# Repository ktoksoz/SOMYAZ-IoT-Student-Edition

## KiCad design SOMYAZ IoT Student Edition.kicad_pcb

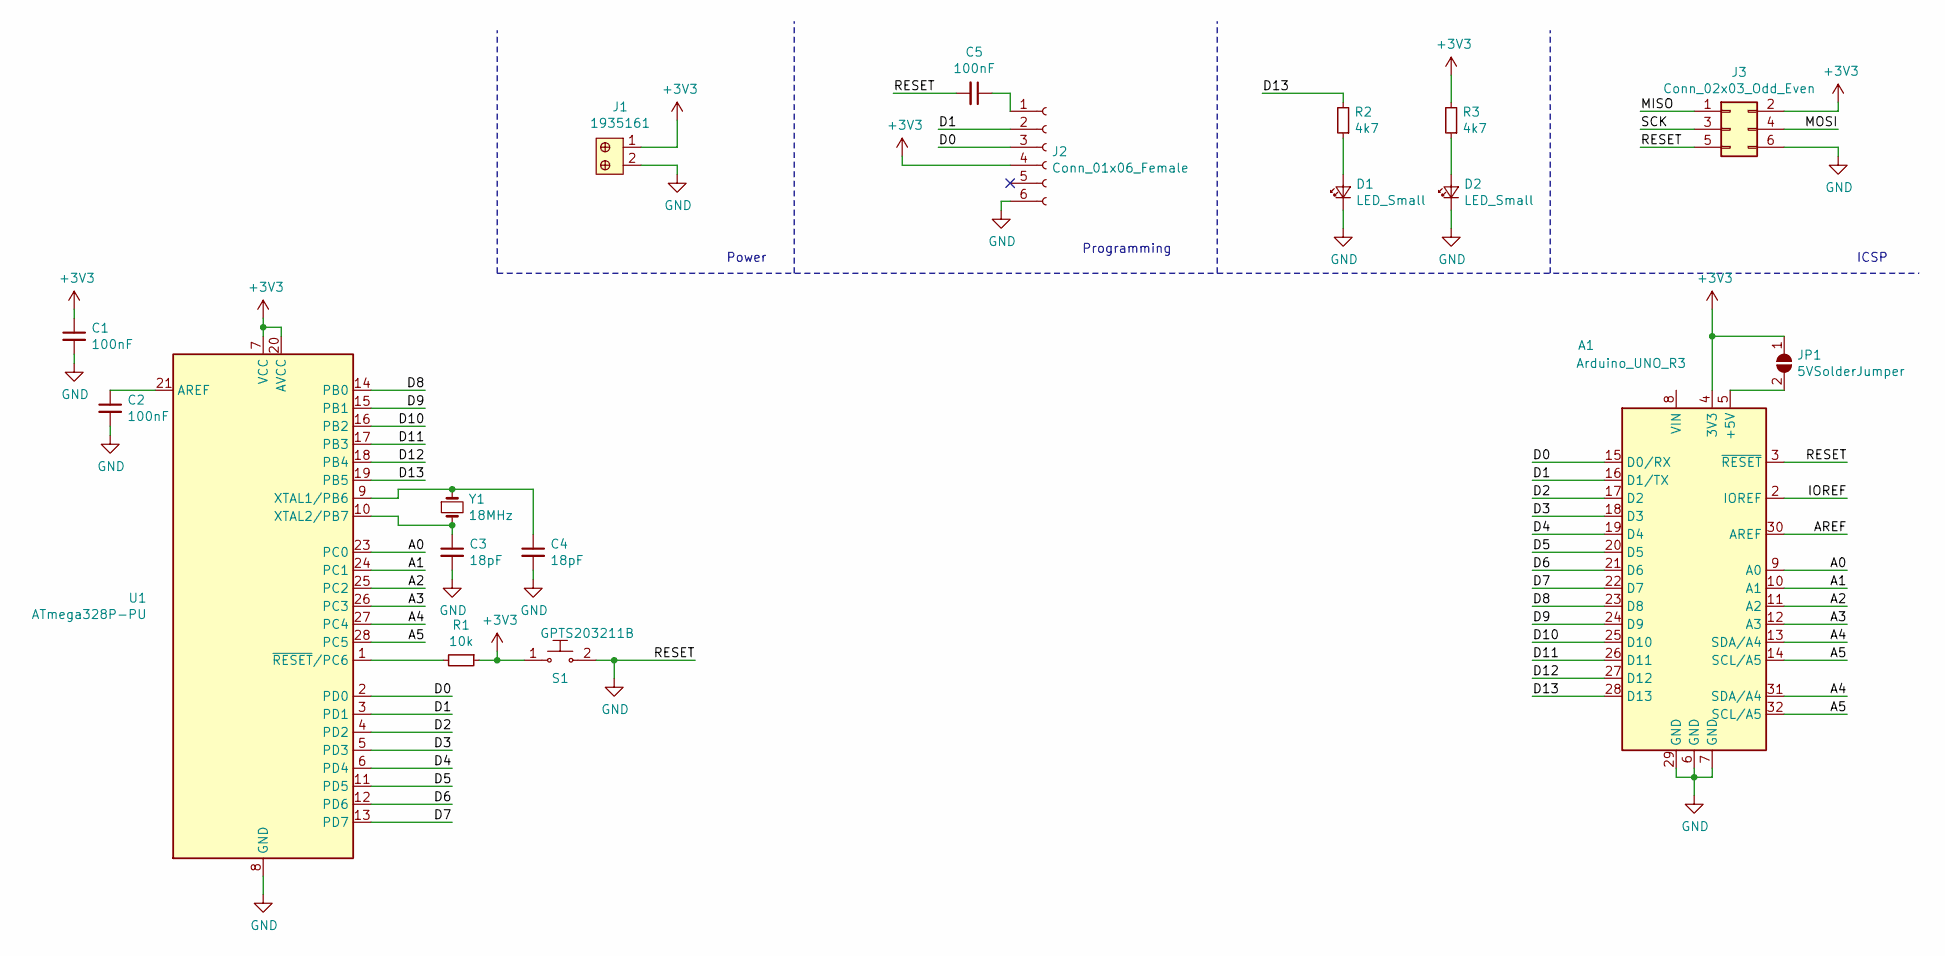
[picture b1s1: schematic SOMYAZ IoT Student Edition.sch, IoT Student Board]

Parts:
A1: Arduino_UNO_R3
C1, C2, C5: 100nF; C_Rect_L7.0mm_W2.5mm_P5.00mm; Digikey-PN BC5229CT-ND
C3, C4: 18pF; C_Rect_L7.0mm_W2.5mm_P5.00mm; Digikey-PN BC1033CT-ND
D1, D2: LED_Small; LED_D5.0mm; Digikey-PN C503B-ACN-CY0Z0252-030CT-ND
J1: 1935161; Terminal_Block_D1.3mm_P5mm; MPN 1935161; Digi-Key_PN 277-1667-ND
J2: Conn_01x06_Female; PinSocket_1x06_P2.54mm_Vertical
J3: Conn_02x03_Odd_Even; PinHeader_2x03_P2.54mm_Vertical
JP1: 5VSolderJumper; SolderJumper-2_P1.3mm_Open_Pad1.0x1.5mm
R1: 10k; R_Axial_DIN0207_L6.3mm_D2.5mm_P10.16mm_Horizontal; Digikey-PN CF14JT10K0CT-ND
R2, R3: 4k7; R_Axial_DIN0207_L6.3mm_D2.5mm_P10.16mm_Horizontal; Digikey-PN CF14JT10K0CT-ND
S1: GPTS203211B; PushButton_12x12mm_THT_GPTS203211B; MPN GPTS203211B; Digi-Key_PN CW181-ND
U1: ATmega328P-PU; DIP-28_W7.62mm; Digikey-PN ATMEGA328P-PU-ND
Y1: 18MHz; Crystal_HC49-U_Vertical; Digikey-PN 535-9062-ND

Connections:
+3V3: A1.4 (3V3), C1.1, J1.1, J2.4, J3.2, JP1.1 (A), R1.1, R3.2, S1.1, U1.7 (VCC), U1.20 (AVCC); also elsewhere on the board
/A0: A1.9 (A0), U1.23 (PC0); also elsewhere on the board
/A1: A1.10 (A1), U1.24 (PC1); also elsewhere on the board
/A2: A1.11 (A2), U1.25 (PC2); also elsewhere on the board
/A3: A1.12 (A3), U1.26 (PC3); also elsewhere on the board
/A4: A1.13 (SDA/A4), A1.31 (SDA/A4), U1.27 (PC4); also elsewhere on the board
/A5: A1.14 (SCL/A5), A1.32 (SCL/A5), U1.28 (PC5); also elsewhere on the board
/D0: A1.15 (D0/RX), J2.3, U1.2 (PD0); also elsewhere on the board
/D1: A1.16 (D1/TX), J2.2, U1.3 (PD1); also elsewhere on the board
/D2: A1.17 (D2), U1.4 (PD2); also elsewhere on the board
/D3: A1.18 (D3), U1.5 (PD3); also elsewhere on the board
/D4: A1.19 (D4), U1.6 (PD4); also elsewhere on the board
/D5: A1.20 (D5), U1.11 (PD5); also elsewhere on the board
/D6: A1.21 (D6), U1.12 (PD6); also elsewhere on the board
/D7: A1.22 (D7), U1.13 (PD7); also elsewhere on the board
/D8: A1.23 (D8), U1.14 (PB0); also elsewhere on the board
/D9: A1.24 (D9), U1.15 (PB1); also elsewhere on the board
/D10: A1.25 (D10), U1.16 (PB2); also elsewhere on the board
/D11: A1.26 (D11), U1.17 (PB3); also elsewhere on the board
/D12: A1.27 (D12), U1.18 (PB4); also elsewhere on the board
/D13: A1.28 (D13), R2.2, U1.19 (PB5); also elsewhere on the board
/MISO: J3.1
/MOSI: J3.4
/SCK: J3.3
GND: A1.3 (~RESET), A1.6 (GND), A1.7 (GND), A1.29 (GND), C1.2, C2.2, C3.2, C4.2, C5.2, D1.1 (K), D2.1 (K), J1.2, J2.6, J3.5, J3.6, S1.2, U1.8 (GND), U1.22 (GND); also elsewhere on the board
unnamed 28: A1.5 (+5V), JP1.2 (B); also elsewhere on the board
unnamed: C2.1, U1.21 (AREF)
unnamed: C3.1, U1.10 (XTAL2/PB7), Y1.2
unnamed: C4.1, U1.9 (XTAL1/PB6), Y1.1
unnamed: C5.1, J2.1
unnamed: D1.2 (A), R2.1
unnamed: D2.2 (A), R3.1
unnamed: R1.2, U1.1 (~RESET~/PC6)

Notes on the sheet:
ICSP
Programming
Power

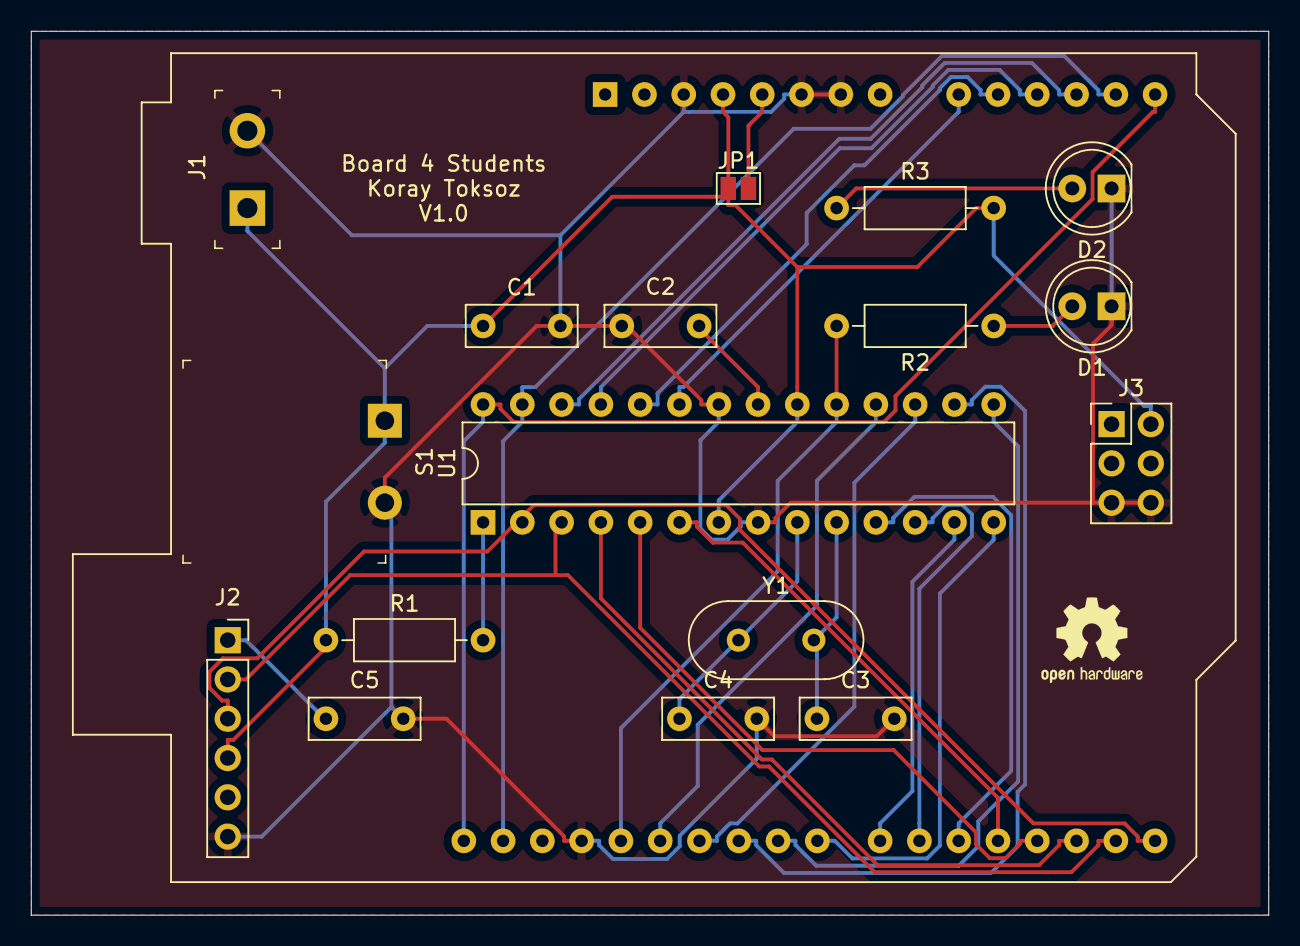
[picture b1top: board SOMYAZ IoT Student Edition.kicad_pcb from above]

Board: 2 copper layers, 80.0 x 57.2 mm, 19 parts (0 on the bottom side), 30 nets.

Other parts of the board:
Arduino: Arduino_UNO_R3
OSHW1: OSHW-Logo2_7.3x6mm_SilkScreen

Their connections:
+3V3: Arduino.4; also elsewhere on the board
/A0: Arduino.9; also elsewhere on the board
/A1: Arduino.10; also elsewhere on the board
/A2: Arduino.11; also elsewhere on the board
/A3: Arduino.12; also elsewhere on the board
/A4: Arduino.13, Arduino.31; also elsewhere on the board
/A5: Arduino.14, Arduino.32; also elsewhere on the board
/D0: Arduino.15; also elsewhere on the board
/D1: Arduino.16; also elsewhere on the board
/D2: Arduino.17; also elsewhere on the board
/D3: Arduino.18; also elsewhere on the board
/D4: Arduino.19; also elsewhere on the board
/D5: Arduino.20; also elsewhere on the board
/D6: Arduino.21; also elsewhere on the board
/D7: Arduino.22; also elsewhere on the board
/D8: Arduino.23; also elsewhere on the board
/D9: Arduino.24; also elsewhere on the board
/D10: Arduino.25; also elsewhere on the board
/D11: Arduino.26; also elsewhere on the board
/D12: Arduino.27; also elsewhere on the board
/D13: Arduino.28; also elsewhere on the board
GND: Arduino.3, Arduino.6, Arduino.7, Arduino.29; also elsewhere on the board
unnamed 28: Arduino.5; also elsewhere on the board
